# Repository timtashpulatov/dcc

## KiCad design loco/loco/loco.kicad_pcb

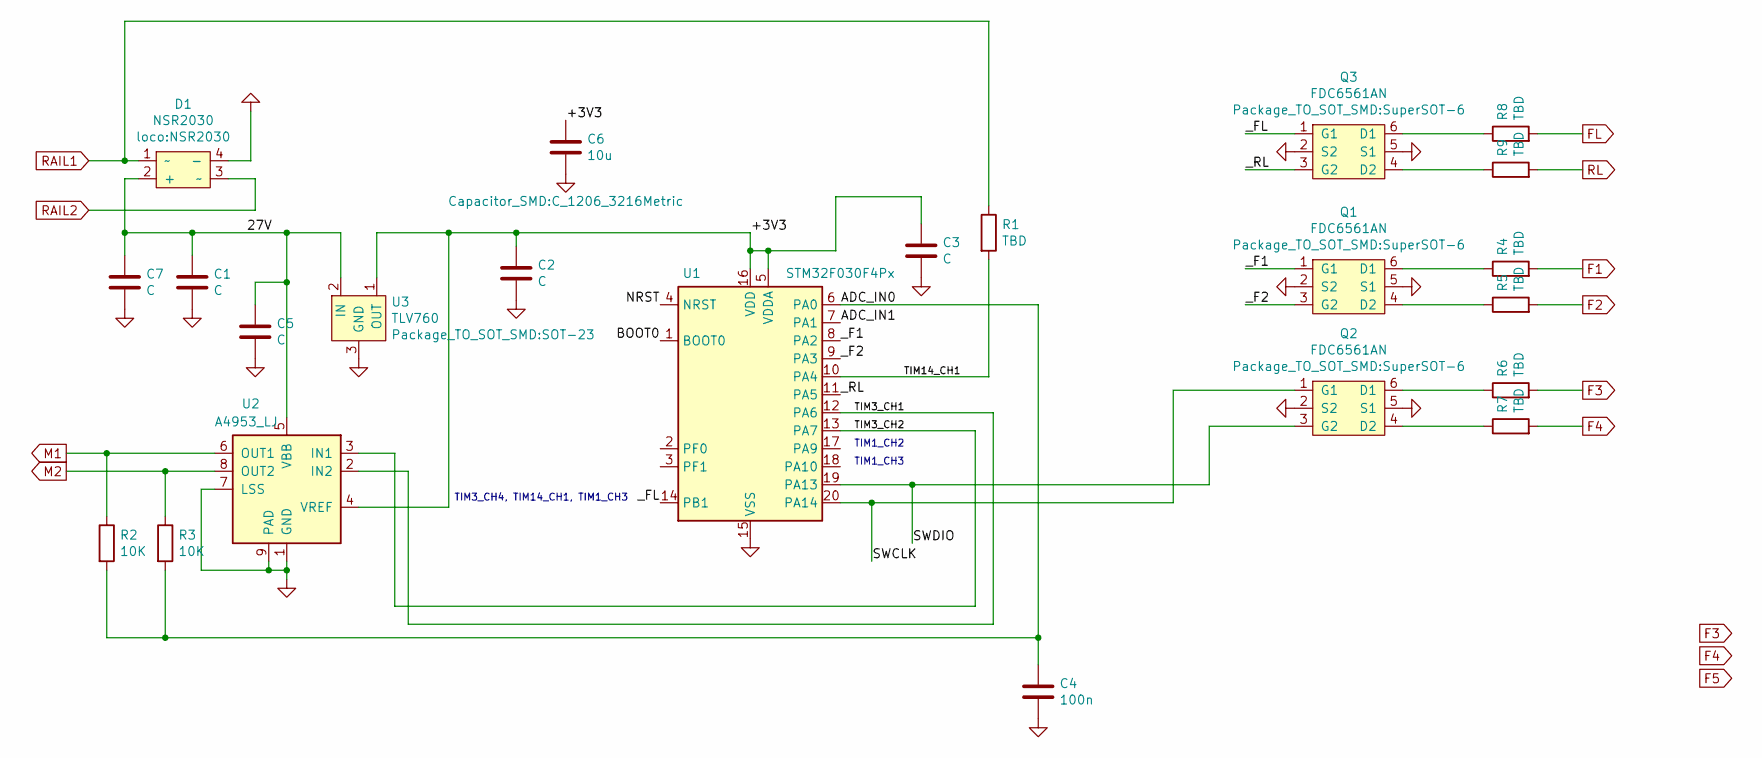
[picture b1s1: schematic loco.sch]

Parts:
C1, C2, C3, C5, C7: C; C_0603_1608Metric
C4: 100n; C_0603_1608Metric
C6: 10u; C_1206_3216Metric
D1: NSR2030
Q1, Q2, Q3: FDC6561AN; SuperSOT-6
R1, R4, R5, R6, R7, R8, R9: TBD; R_0603_1608Metric
R2, R3: 10K; R_0603_1608Metric
U1: STM32F030F4Px; TSSOP-20_4.4x6.5mm_P0.65mm
U2: A4953_LJ; SOIC-8-1EP_3.9x4.9mm_P1.27mm_EP2.41x3.3mm
U3: TLV760; SOT-23

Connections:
/27V: C1.1, C5.1, C7.1, D1.2 (+), U2.5 (VBB), U3.2 (IN)
/+3V3: C2.1, C3.1, C6.1, U1.5 (VDDA), U1.16 (VDD), U2.4 (VREF), U3.1 (OUT)
/ADC_IN0: C4.1, R2.2, R3.2, U1.6 (PA0)
/ADC_IN1: U1.7 (PA1)
/BOOT0: U1.1 (BOOT0)
/NRST: U1.4 (NRST)
/SWCLK: Q2.1 (G1), U1.20 (PA14)
/SWDIO: Q2.3 (G2), U1.19 (PA13)
/TIM3_CH1: U1.12 (PA6), U2.2 (IN2)
/TIM3_CH2: U1.13 (PA7), U2.3 (IN1)
/TIM14_CH1: R1.2, U1.10 (PA4)
/_F1: Q1.1 (G1), U1.8 (PA2)
/_F2: Q1.3 (G2), U1.9 (PA3)
/_FL: Q3.1 (G1), U1.14 (PB1)
/_RL: Q3.3 (G2), U1.11 (PA5)
F1: R4.2
F2: R5.2
F3: R6.2
F4: R7.2
FL: R8.2
GND: C1.2, C2.2, C3.2, C4.2, C5.2, C6.2, C7.2, D1.4 (-), Q1.2 (S2), Q1.5 (S1), Q2.2 (S2), Q2.5 (S1), Q3.2 (S2), Q3.5 (S1), U1.15 (VSS), U2.1 (GND), U2.7 (LSS), U2.9 (PAD), U3.3 (GND)
M1: R2.1, U2.6 (OUT1)
M2: R3.1, U2.8 (OUT2)
unnamed: Q1.4 (D2), R5.1
unnamed: Q1.6 (D1), R4.1
unnamed: Q2.4 (D2), R7.1
unnamed: Q2.6 (D1), R6.1
unnamed: Q3.4 (D2), R9.1
unnamed: Q3.6 (D1), R8.1
RAIL1: D1.1 (~~), R1.1
RAIL2: D1.3 (~~)
RL: R9.2

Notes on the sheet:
TIM3_CH4, TIM14_CH1, TIM1_CH3
TIM1_CH2
TIM1_CH3

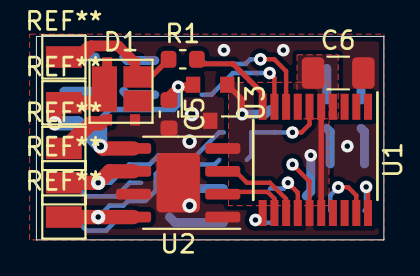
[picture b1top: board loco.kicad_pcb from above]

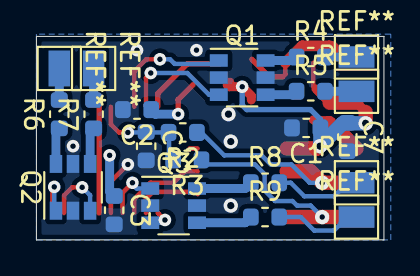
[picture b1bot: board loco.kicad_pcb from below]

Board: 2 copper layers, 19.3 x 11.3 mm, 23 parts (16 on the bottom side), 22 nets.

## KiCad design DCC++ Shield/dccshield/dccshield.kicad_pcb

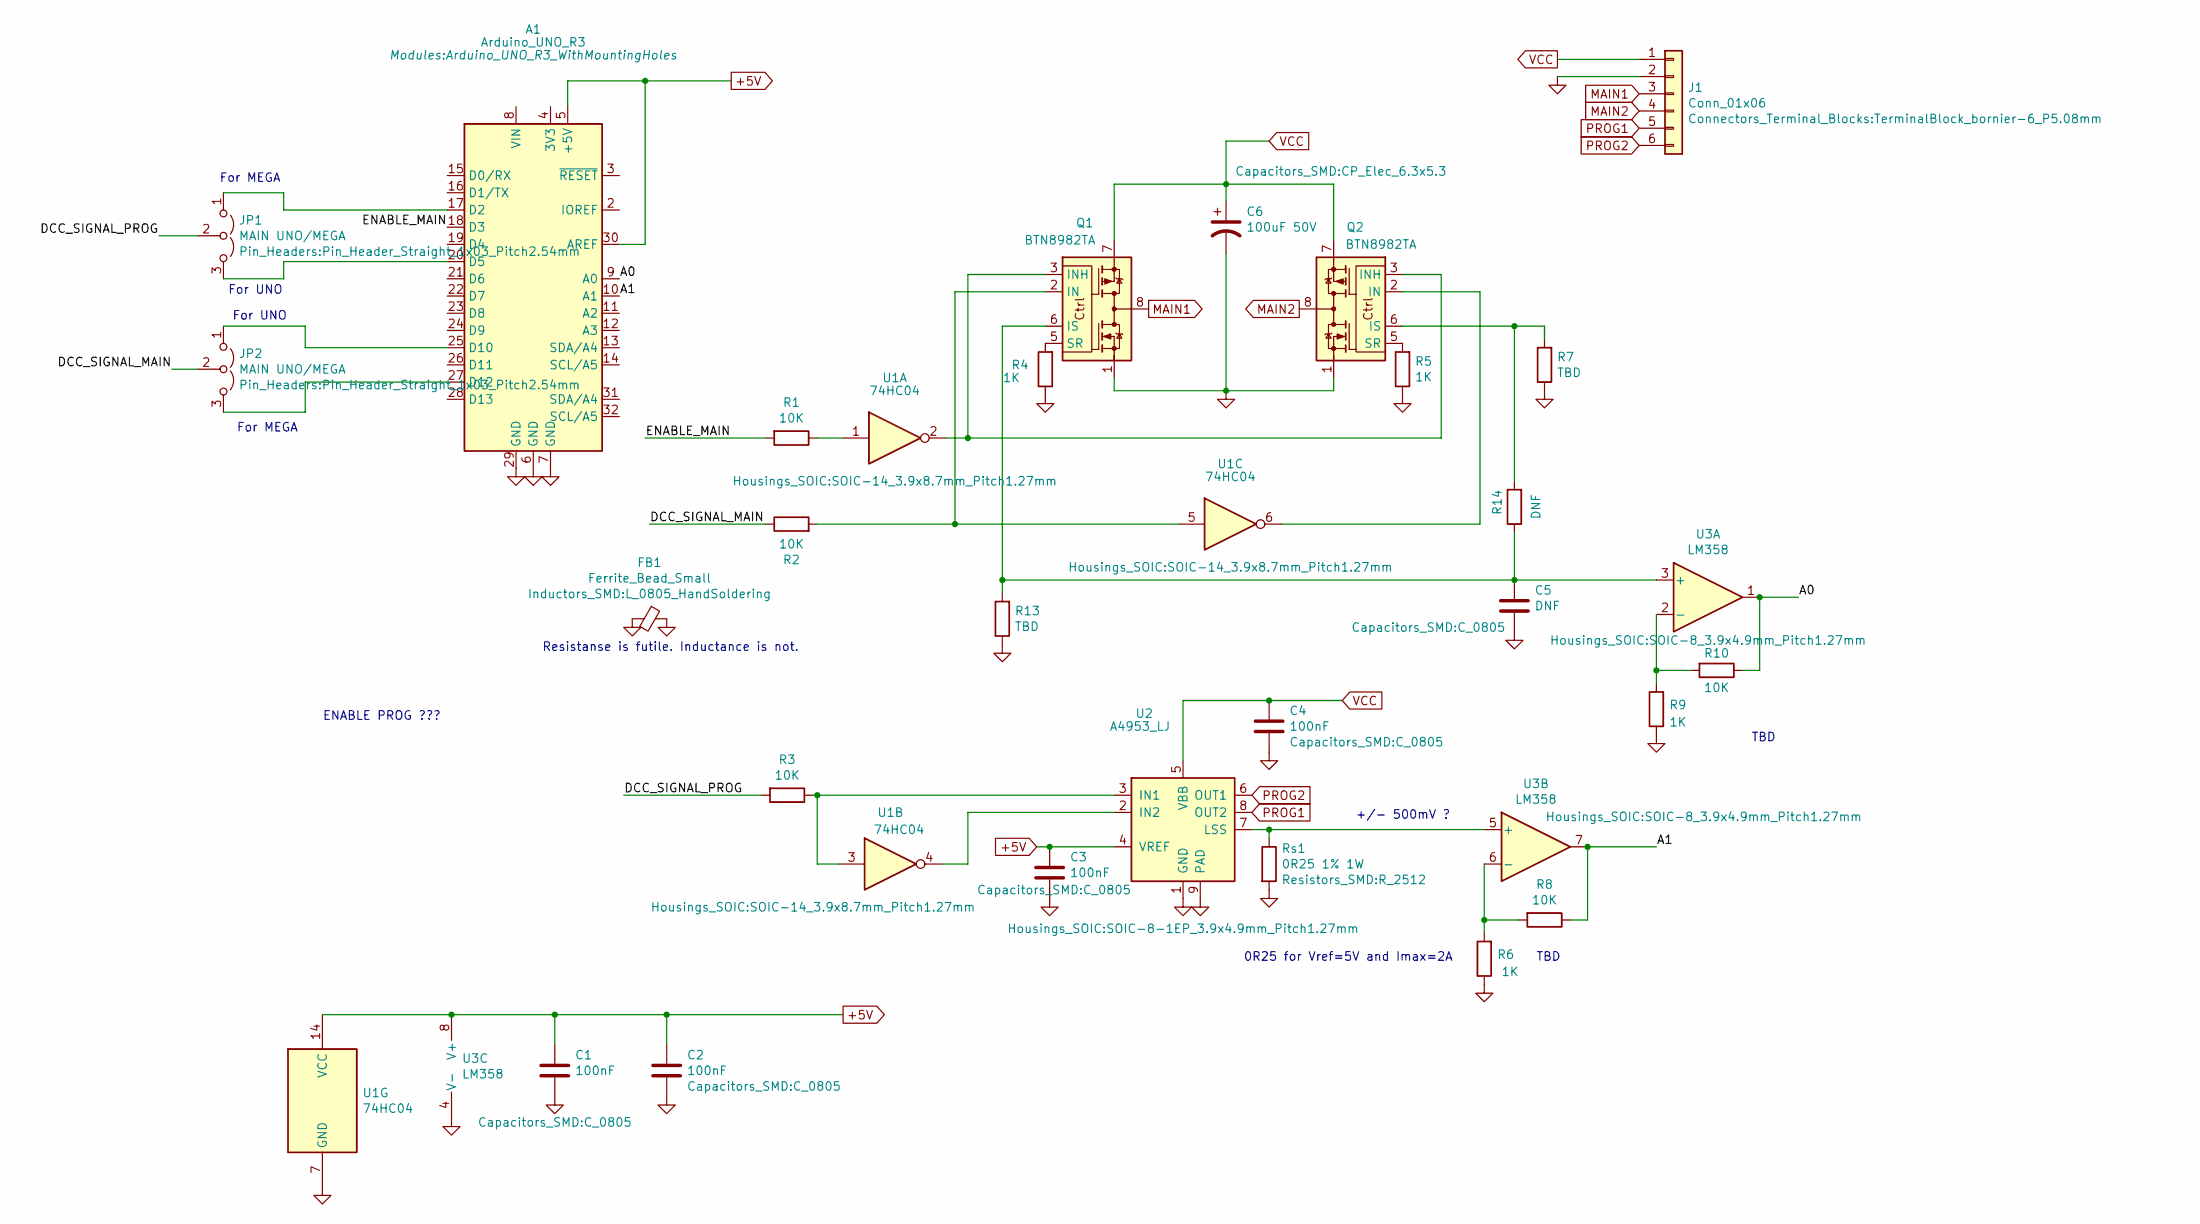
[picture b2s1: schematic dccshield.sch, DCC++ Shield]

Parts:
A1: Arduino_UNO_R3; Arduino_UNO_R3_WithMountingHoles
C1, C2, C3, C4: 100nF; C_0805
C5: DNF; C_0805
C6: 100uF 50V; CP_Elec_6.3x5.3
FB1: Ferrite_Bead_Small; L_0805_HandSoldering
J1: Conn_01x06; TerminalBlock_bornier-6_P5.08mm
JP1, JP2: MAIN UNO/MEGA; Pin_Header_Straight_1x03_Pitch2.54mm
Q1, Q2: BTN8982TA; TO-263-7_TabPin8
R1, R2, R3, R8, R10: 10K; R_0805
R4, R5, R6, R9: 1K; R_0805
R7, R13: TBD; R_0805
R14: DNF; R_0805
Rs1: 0R25 1% 1W; R_2512
U1: 74HC04; SOIC-14_3.9x8.7mm_Pitch1.27mm
U2: A4953_LJ; SOIC-8-1EP_3.9x4.9mm_Pitch1.27mm
U3: LM358; SOIC-8_3.9x4.9mm_Pitch1.27mm

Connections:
+5V: A1.5 (+5V), A1.30 (AREF), C1.1, C2.1, C3.1, U1.14 (VCC), U2.4 (VREF), U3.8 (V+)
/A0: A1.9 (A0), R10.1, U3.1
/A1: A1.10 (A1), R8.1, U3.7
/DCC_SIGNAL_MAIN: JP2.2 (C), R2.1
/DCC_SIGNAL_PROG: JP1.2 (C), R3.2
/ENABLE_MAIN: A1.18 (D3), R1.2
GND: A1.6 (GND), A1.7 (GND), A1.29 (GND), C1.2, C2.2, C3.2, C4.2, C5.2, C6.2, FB1.1, FB1.2, J1.2, Q1.1, Q2.1, R4.1, R5.1, R6.1, R7.1, R9.1, R13.1, Rs1.2, U1.7 (GND), U2.1 (GND), U2.9 (PAD), U3.4 (V-)
MAIN1: J1.3, Q1.4, Q1.8
MAIN2: J1.4, Q2.4, Q2.8
unnamed: A1.17 (D2), JP1.1 (A)
unnamed: A1.20 (D5), JP1.3 (B)
unnamed: A1.25 (D10), JP2.1 (A)
unnamed: A1.27 (D12), JP2.3 (B)
unnamed: C5.1, Q1.6 (IS), R13.2, R14.1, U3.3 (+)
unnamed: Q1.2 (IN), R2.2, U1.5
unnamed: Q1.3 (INH), Q2.3 (INH), U1.2
unnamed: Q1.5 (SR), R4.2
unnamed: Q2.2 (IN), U1.6
unnamed: Q2.5 (SR), R5.2
unnamed: Q2.6 (IS), R7.2, R14.2
unnamed: R1.1, U1.1
unnamed: R3.1, U1.3, U2.3 (IN1)
unnamed: R6.2, R8.2, U3.6 (-)
unnamed: R9.2, R10.2, U3.2 (-)
unnamed: Rs1.1, U2.7 (LSS), U3.5 (+)
unnamed: U1.4, U2.2 (IN2)
PROG1: J1.5, U2.8 (OUT2)
PROG2: J1.6, U2.6 (OUT1)
VCC: C4.1, C6.1, J1.1, Q1.7, Q2.7, U2.5 (VBB)

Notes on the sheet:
+/- 500mV ?
0R25 for Vref=5V and Imax=2A
TBD
ENABLE PROG ???
Resistanse is futile. Inductance is not.
For UNO
For MEGA

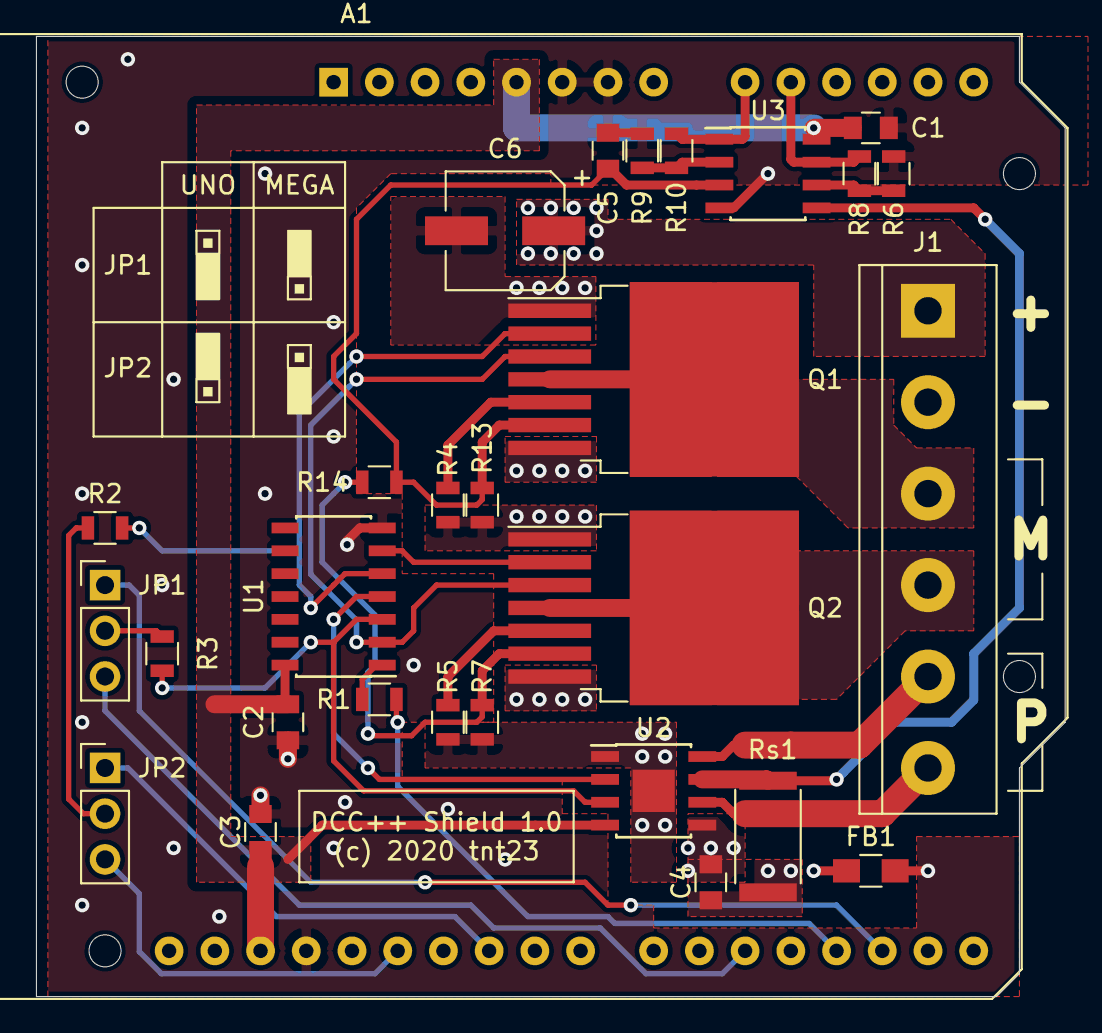
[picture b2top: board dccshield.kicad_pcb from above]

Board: 2 copper layers, 57.2 x 53.3 mm, 29 parts (0 on the bottom side), 29 nets.

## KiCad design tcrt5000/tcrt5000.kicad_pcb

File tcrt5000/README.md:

Optical detector using TCRT5000 sensor from Vishay

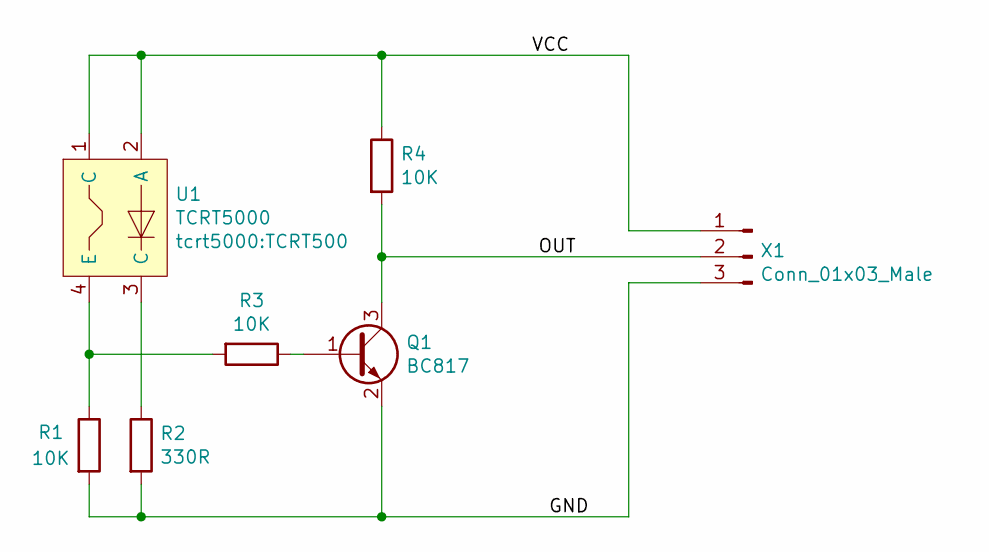
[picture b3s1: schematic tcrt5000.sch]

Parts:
Q1: BC817; SOT-23
R1, R3, R4: 10K; R_0805_2012Metric
R2: 330R; R_0805_2012Metric
U1: TCRT5000; TCRT500
X1: Conn_01x03_Male; PinHeader_1x03_P2.54mm_Vertical

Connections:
/GND: Q1.2 (E), R1.2, R2.2, X1.3
/OUT: Q1.3 (C), R4.2, X1.2
/VCC: R4.1, U1.1 (C), U1.2 (A), X1.1
unnamed: Q1.1 (B), R3.1
unnamed: R1.1, R3.2, U1.4 (E)
unnamed: R2.1, U1.3 (C)

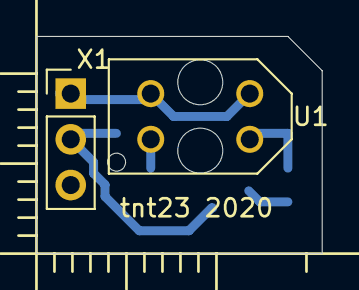
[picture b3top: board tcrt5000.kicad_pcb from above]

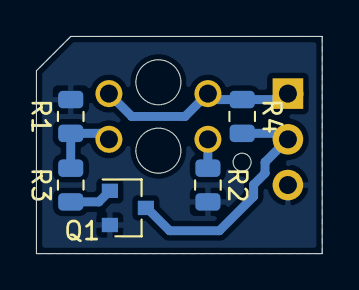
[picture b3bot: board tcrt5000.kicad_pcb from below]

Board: 2 copper layers, 15.9 x 12.1 mm, 7 parts (5 on the bottom side), 6 nets.

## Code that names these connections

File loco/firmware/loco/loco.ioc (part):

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Mcu.Name=STM32F030F4Px
Mcu.Package=TSSOP20
Mcu.UserName=STM32F030F4Px
PA0.Mode=IN0
PA0.Signal=ADC_IN0
PA13.Mode=Serial_Wire
PA13.Signal=SYS_SWDIO
PA14.Mode=Serial_Wire
PA14.Signal=SYS_SWCLK
PA2.GPIOParameters=GPIO_Label
PA2.GPIO_Label=F1
PA2.Signal=GPIO_Output
PA3.GPIOParameters=GPIO_Label
PA3.GPIO_Label=F2
PA3.Signal=GPIO_Output
PA4.Signal=S_TIM14_CH1
PA5.GPIOParameters=GPIO_Label
PA5.GPIO_Label=RL
PA5.Signal=GPIO_Output
PA6.Signal=S_TIM3_CH1
PA7.Signal=S_TIM3_CH2
PB1.GPIOParameters=GPIO_Label
PB1.GPIO_Label=FL
PB1.Signal=GPIO_Output
RCC.SYSCLKFreq_VALUE=48000000
RCC.SYSCLKSource=RCC_SYSCLKSOURCE_PLLCLK
board=custom

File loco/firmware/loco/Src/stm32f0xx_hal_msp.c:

/* USER CODE BEGIN Header */
/**
  ******************************************************************************
  * File Name          : stm32f0xx_hal_msp.c
  * Description        : This file provides code for the MSP Initialization 
  *                      and de-Initialization codes.
  ******************************************************************************
  * @attention
  *
  * <h2><center>&copy; Copyright (c) 2020 STMicroelectronics.
  * All rights reserved.</center></h2>
  *
  * This software component is licensed by ST under BSD 3-Clause license,
  * the "License"; You may not use this file except in compliance with the
  * License. You may obtain a copy of the License at:
  *                        opensource.org/licenses/BSD-3-Clause
  *
  ******************************************************************************
  */
/* USER CODE END Header */

/* Includes ------------------------------------------------------------------*/
#include "main.h"
/* USER CODE BEGIN Includes */

/* USER CODE END Includes */

extern DMA_HandleTypeDef hdma_adc;

/* Private typedef -----------------------------------------------------------*/
/* USER CODE BEGIN TD */

/* USER CODE END TD */

/* Private define ------------------------------------------------------------*/
/* USER CODE BEGIN Define */
 
/* USER CODE END Define */

/* Private macro -------------------------------------------------------------*/
/* USER CODE BEGIN Macro */

/* USER CODE END Macro */

/* Private variables ---------------------------------------------------------*/
/* USER CODE BEGIN PV */

/* USER CODE END PV */

/* Private function prototypes -----------------------------------------------*/
/* USER CODE BEGIN PFP */

/* USER CODE END PFP */

/* External functions --------------------------------------------------------*/
/* USER CODE BEGIN ExternalFunctions */

/* USER CODE END ExternalFunctions */

/* USER CODE BEGIN 0 */

/* USER CODE END 0 */
                        
void HAL_TIM_MspPostInit(TIM_HandleTypeDef *htim);
                    /**
  * Initializes the Global MSP.
  */
void HAL_MspInit(void)
{
  /* USER CODE BEGIN MspInit 0 */

  /* USER CODE END MspInit 0 */

  __HAL_RCC_SYSCFG_CLK_ENABLE();
  __HAL_RCC_PWR_CLK_ENABLE();

  /* System interrupt init*/

  /* USER CODE BEGIN MspInit 1 */

  /* USER CODE END MspInit 1 */
}

/**
* @brief ADC MSP Initialization
* This function configures the hardware resources used in this example
* @param hadc: ADC handle pointer
* @retval None
*/
void HAL_ADC_MspInit(ADC_HandleTypeDef* hadc)
{
  GPIO_InitTypeDef GPIO_InitStruct = {0};
  if(hadc->Instance==ADC1)
  {
  /* USER CODE BEGIN ADC1_MspInit 0 */

  /* USER CODE END ADC1_MspInit 0 */
    /* Peripheral clock enable */
    __HAL_RCC_ADC1_CLK_ENABLE();
  
    __HAL_RCC_GPIOA_CLK_ENABLE();
    /**ADC GPIO Configuration    
    PA0     ------> ADC_IN0 
    */
    GPIO_InitStruct.Pin = GPIO_PIN_0;
    GPIO_InitStruct.Mode = GPIO_MODE_ANALOG;
    GPIO_InitStruct.Pull = GPIO_NOPULL;
    HAL_GPIO_Init(GPIOA, &GPIO_InitStruct);

    /* ADC1 DMA Init */
    /* ADC Init */
    hdma_adc.Instance = DMA1_Channel1;
    hdma_adc.Init.Direction = DMA_PERIPH_TO_MEMORY;
    hdma_adc.Init.PeriphInc = DMA_PINC_DISABLE;
    hdma_adc.Init.MemInc = DMA_MINC_ENABLE;
    hdma_adc.Init.PeriphDataAlignment = DMA_PDATAALIGN_HALFWORD;
    hdma_adc.Init.MemDataAlignment = DMA_MDATAALIGN_HALFWORD;
    hdma_adc.Init.Mode = DMA_NORMAL;
    hdma_adc.Init.Priority = DMA_PRIORITY_LOW;
    if (HAL_DMA_Init(&hdma_adc) != HAL_OK)
    {
      Error_Handler();
    }

    __HAL_LINKDMA(hadc,DMA_Handle,hdma_adc);


  /* USER CODE BEGIN ADC1_MspInit 1 */

  /* USER CODE END ADC1_MspInit 1 */
  }

}

/**
* @brief ADC MSP De-Initialization
* This function freeze the hardware resources used in this example
* @param hadc: ADC handle pointer
* @retval None
*/
void HAL_ADC_MspDeInit(ADC_HandleTypeDef* hadc)
{
  if(hadc->Instance==ADC1)
  {
  /* USER CODE BEGIN ADC1_MspDeInit 0 */

  /* USER CODE END ADC1_MspDeInit 0 */
    /* Peripheral clock disable */
    __HAL_RCC_ADC1_CLK_DISABLE();
  
    /**ADC GPIO Configuration    
    PA0     ------> ADC_IN0 
    */
    HAL_GPIO_DeInit(GPIOA, GPIO_PIN_0);

  /* USER CODE BEGIN ADC1_MspDeInit 1 */

  /* USER CODE END ADC1_MspDeInit 1 */
  }

}

/**
* @brief TIM_Base MSP Initialization
* This function configures the hardware resources used in this example
* @param htim_base: TIM_Base handle pointer
* @retval None
*/
void HAL_TIM_Base_MspInit(TIM_HandleTypeDef* htim_base)
{
  GPIO_InitTypeDef GPIO_InitStruct = {0};
  if(htim_base->Instance==TIM3)
  {
  /* USER CODE BEGIN TIM3_MspInit 0 */

  /* USER CODE END TIM3_MspInit 0 */
    /* Peripheral clock enable */
    __HAL_RCC_TIM3_CLK_ENABLE();
  /* USER CODE BEGIN TIM3_MspInit 1 */

  /* USER CODE END TIM3_MspInit 1 */
  }
  else if(htim_base->Instance==TIM14)
  {
  /* USER CODE BEGIN TIM14_MspInit 0 */

  /* USER CODE END TIM14_MspInit 0 */
    /* Peripheral clock enable */
    __HAL_RCC_TIM14_CLK_ENABLE();
  
    __HAL_RCC_GPIOA_CLK_ENABLE();
    /**TIM14 GPIO Configuration    
    PA4     ------> TIM14_CH1 
    */
    GPIO_InitStruct.Pin = GPIO_PIN_4;
    GPIO_InitStruct.Mode = GPIO_MODE_AF_PP;
    GPIO_InitStruct.Pull = GPIO_NOPULL;
    GPIO_InitStruct.Speed = GPIO_SPEED_FREQ_LOW;
    GPIO_InitStruct.Alternate = GPIO_AF4_TIM14;
    HAL_GPIO_Init(GPIOA, &GPIO_InitStruct);

    /* TIM14 interrupt Init */
    HAL_NVIC_SetPriority(TIM14_IRQn, 0, 0);
    HAL_NVIC_EnableIRQ(TIM14_IRQn);
  /* USER CODE BEGIN TIM14_MspInit 1 */

  /* USER CODE END TIM14_MspInit 1 */
  }

}

void HAL_TIM_MspPostInit(TIM_HandleTypeDef* htim)
{
  GPIO_InitTypeDef GPIO_InitStruct = {0};
  if(htim->Instance==TIM3)
  {
  /* USER CODE BEGIN TIM3_MspPostInit 0 */

  /* USER CODE END TIM3_MspPostInit 0 */
  
    __HAL_RCC_GPIOA_CLK_ENABLE();
    /**TIM3 GPIO Configuration    
    PA6     ------> TIM3_CH1
    PA7     ------> TIM3_CH2 
    */
    GPIO_InitStruct.Pin = GPIO_PIN_6|GPIO_PIN_7;
    GPIO_InitStruct.Mode = GPIO_MODE_AF_PP;
    GPIO_InitStruct.Pull = GPIO_PULLDOWN;	// GPIO_NOPULL;
    GPIO_InitStruct.Speed = GPIO_SPEED_FREQ_HIGH;	//GPIO_SPEED_FREQ_LOW;
    GPIO_InitStruct.Alternate = GPIO_AF1_TIM3;
    HAL_GPIO_Init(GPIOA, &GPIO_InitStruct);

  /* USER CODE BEGIN TIM3_MspPostInit 1 */

  /* USER CODE END TIM3_MspPostInit 1 */
  }

}
/**
* @brief TIM_Base MSP De-Initialization
* This function freeze the hardware resources used in this example
* @param htim_base: TIM_Base handle pointer
* @retval None
*/
void HAL_TIM_Base_MspDeInit(TIM_HandleTypeDef* htim_base)
{
  if(htim_base->Instance==TIM3)
  {
  /* USER CODE BEGIN TIM3_MspDeInit 0 */

  /* USER CODE END TIM3_MspDeInit 0 */
    /* Peripheral clock disable */
    __HAL_RCC_TIM3_CLK_DISABLE();
  /* USER CODE BEGIN TIM3_MspDeInit 1 */

  /* USER CODE END TIM3_MspDeInit 1 */
  }
  else if(htim_base->Instance==TIM14)
  {
  /* USER CODE BEGIN TIM14_MspDeInit 0 */

  /* USER CODE END TIM14_MspDeInit 0 */
    /* Peripheral clock disable */
    __HAL_RCC_TIM14_CLK_DISABLE();
  
    /**TIM14 GPIO Configuration    
    PA4     ------> TIM14_CH1 
    */
    HAL_GPIO_DeInit(GPIOA, GPIO_PIN_4);

    /* TIM14 interrupt DeInit */
    HAL_NVIC_DisableIRQ(TIM14_IRQn);
  /* USER CODE BEGIN TIM14_MspDeInit 1 */

  /* USER CODE END TIM14_MspDeInit 1 */
  }

}

/* USER CODE BEGIN 1 */

/* USER CODE END 1 */

/************************ (C) COPYRIGHT STMicroelectronics *****END OF FILE****/

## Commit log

2020-01-23 Initial
2020-01-24 Mask updated
2020-01-24 3d STEP model added
2020-01-24 Misc
2020-01-24 Gerbers done
2020-01-27 LED resistor calculations added
2020-01-28 Add new project DCC Shield
2020-01-29 PCB update
2020-01-29 3d models added
2020-01-30 Gerbers, docs
2020-02-10 Update and gerbers
2020-02-29 Fab layer update
2020-03-02 Update for BOM
2020-03-08 Initial loco commit
2020-03-08 Loco update
2020-03-08 FR and RL
2020-03-08 F1 and F2
2020-03-09 Docs added
2020-03-09 Routing done, mostly
2020-03-09 3d model of bridge added
2020-03-10 Add gerbers, initial project sources
2020-03-11 Whip frequency to 48MHz
2020-03-12 SWD debug speed update
2020-03-12 Enable TIM14 ints
2020-03-13 Input capture works
2020-03-13 Debug update
2020-03-14 Debug bits
2020-03-14 Auto invert polarity for Input Capture
2020-03-14 Refactor
2020-03-15 Fixed silly bug due to formatting
2020-03-15 Add decode code
2020-03-15 Speed setting works
2020-03-15 Start second PWM channel
2020-03-15 Add F1 and F2 funcs, F3 and F4 muxed with SWDIO
2020-03-15 More Advanced Subfunctions
2020-03-15 Cleanups
2020-03-15 CV docs
2020-03-16 Initial flash code
2020-03-16 Flash signature
2020-03-17 CV section in flash
2020-03-17 CV heat
2020-03-17 Init flash with default CVs
2020-03-18 Write CV to flash as two bytes
2020-03-18 ReadCV works
2020-03-18 UpdateCV WIP
2020-03-18 TIM3 update
2020-03-18 TIM3 update, again
2020-03-19 Docs
2020-03-19 Prepare for Service Mode
2020-03-19 Ignore fp-info-cache
2020-03-19 Add motor control functions
2020-03-19 Motor accel/decel update
2020-03-19 Add basic ack
2020-03-19 Add Functions
2020-03-19 Motor control update
2020-03-19 Fix acc/dec rate
2020-03-19 Prototypical FL/RL behavior when switching directions under accel/decel
2020-03-19 Ack length set to 5ms
2020-03-19 Service mode WIP
2020-03-19 Service mode Verify WIP
2020-03-20 Do not ack unsupported CVs
2020-03-20 Increase PWM steps to 1024
2020-03-20 CV2 support
2020-03-21 Fix VStart
2020-03-21 Update to Kick
2020-03-21 Prepare for OPS programming
2020-03-21 Write CV to flash works
2020-03-21 Update to CVs
2020-03-21 Kick update
2020-03-21 Cleanup
2020-03-21 Refactor for Headlight
2020-03-21 Fix output mapping for F4
2020-03-21 Functions WIP
2020-03-21 Prepare for soft PWM
2020-03-21 Default CV values
2020-03-22 Add bit manipulation to Service Mode instructions
2020-03-22 Fix bug with flash update
2020-03-22 Fix Functions
2020-03-22 Custom CV64 for Kick time
2020-03-22 Fix CV64 handling
2020-03-22 Outputs WIP
2020-03-23 React only to packets addressed to us
2020-03-23 Add broadcast address
2020-03-23 Control FL/RL with F0
2020-03-23 CV29 bit 0 support
2020-03-24 Towards MERG Lighting FX
2020-03-26 LDO replacement
2020-03-27 Values update
2020-03-28 Cache functions
2020-03-28 Add Extended Addressing
2020-03-28 Prepare for Forward and Reverse Trim
2020-03-28 Trim uncertainity
2020-03-28 Prepare for ADC
2020-03-29 BEMF code commented out
2020-03-30 Update TIM3 mostly
2020-03-30 More BEMF code
2020-03-30 BEMF screenshots
2020-03-30 Add DMA for ADC
2020-03-30 ADC/DMA frenzy
2020-03-30 DMA works (and we are almost out of flash space)
2020-03-30 Update to ADC/DMA
2020-03-31 Fiddling with BEMF
2020-03-31 Minor update
2020-03-31 Use TIM16
2020-05-21 Clean master

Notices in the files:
DCC++ Shield/dccshield/dccshield.kicad_pcb:
(c) 2020 tnt23
